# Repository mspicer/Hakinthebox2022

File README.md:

# Hack-in-the-box 2022 Badge Guide

- PCB.md contains the schematics and pcb layout for each board. This may be helpful for assembly or programming.
- PROGRAM.md contains information on flashing the boards with the current or custom code if desired.

## Assembly

### Step 1
- Solder the attiny85 to the base pcb.

### Step 2
- Solder the first two leds on the base pcb.

### Step 3
- Solder the last two leds on the base pcb.

### Step 4
- Solder the first two leds on the top of the upper pcb.

### Step 5
- Solder the next two leds on the top of the upper pcb.

### Step 6
- Solder the first two leds on the bottom of the upper pcb.

### Step 7
- Solder the last two leds on the upper pcb.

### Step 8
- Solder the headers on the board by first placing them in the expansion board or similar and then slide the board on to ensure good fit.

### Step 9

### Step 10
- Remove the stripped ends of the three solid-core wires and attach them to the base pcb.

### Step 11
- Solder the solid-core wires to the top. The easiest way is to solder the outer two wires, bend them all 90 degrees, then solder the middle one.

### Step 12
- Attach the stand offs to the base pcb with the socket cap screws.

### Step 13

### Step 14
- With the other screws attach the acrylic and the upper pcb to the standoffs.

### Step 15

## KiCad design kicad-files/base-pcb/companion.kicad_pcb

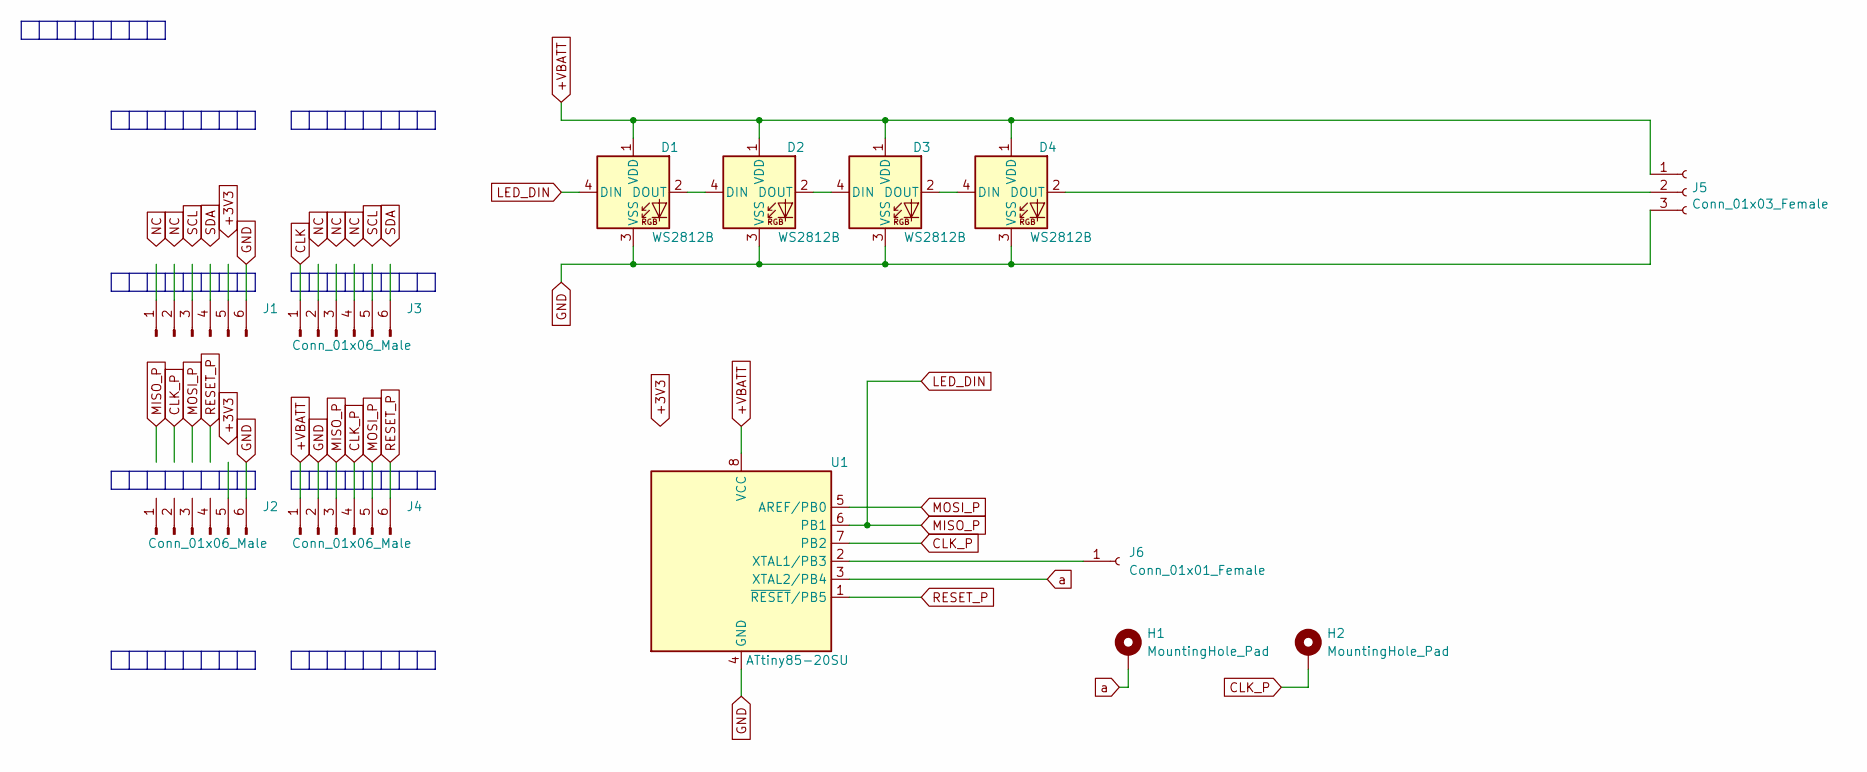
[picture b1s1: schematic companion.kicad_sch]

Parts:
D1, D2, D3, D4: WS2812B; LED_WS2812B_PLCC4_5.0x5.0mm_P3.2mm
H1, H2: MountingHole_Pad; MountingHole_4.3mm_M4_DIN965_Pad_TopOnly
J1, J2, J3, J4: Conn_01x06_Male; PinHeader_1x06_P2.54mm_Vertical
J5: Conn_01x03_Female; PinHeader_1x03_P2.54mm_Vertical_SMD_Pin1Left
J6: Conn_01x01_Female; SolderWirePad_1x01_SMD_1x2mm
U1: ATtiny85-20SU; SOIJ-8_5.3x5.3mm_P1.27mm

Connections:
+VBATT: D1.1 (VDD), D2.1 (VDD), D3.1 (VDD), D4.1 (VDD), J4.1, J5.1, U1.8 (VCC)
CLK: J3.1
CLK_P: H2.1, J4.4, U1.7 (PB2)
GND: D1.3 (VSS), D2.3 (VSS), D3.3 (VSS), D4.3 (VSS), J1.6, J2.6, J4.2, J5.3, U1.4 (GND)
LED_DIN: D1.4 (DIN), J4.3, U1.6 (PB1)
MOSI_P: J4.5, U1.5 (AREF/PB0)
unnamed: D1.2 (DOUT), D2.4 (DIN)
unnamed: D2.2 (DOUT), D3.4 (DIN)
unnamed: D3.2 (DOUT), D4.4 (DIN)
unnamed: D4.2 (DOUT), J5.2
unnamed: J6.1, U1.2 (XTAL1/PB3)
RESET_P: J4.6, U1.1 (~RESET/PB5)
a: H1.1, U1.3 (XTAL2/PB4)

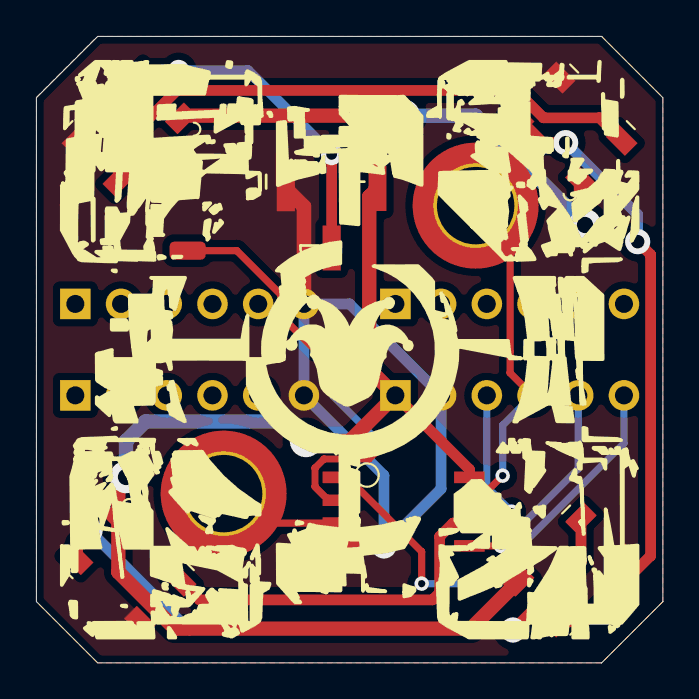
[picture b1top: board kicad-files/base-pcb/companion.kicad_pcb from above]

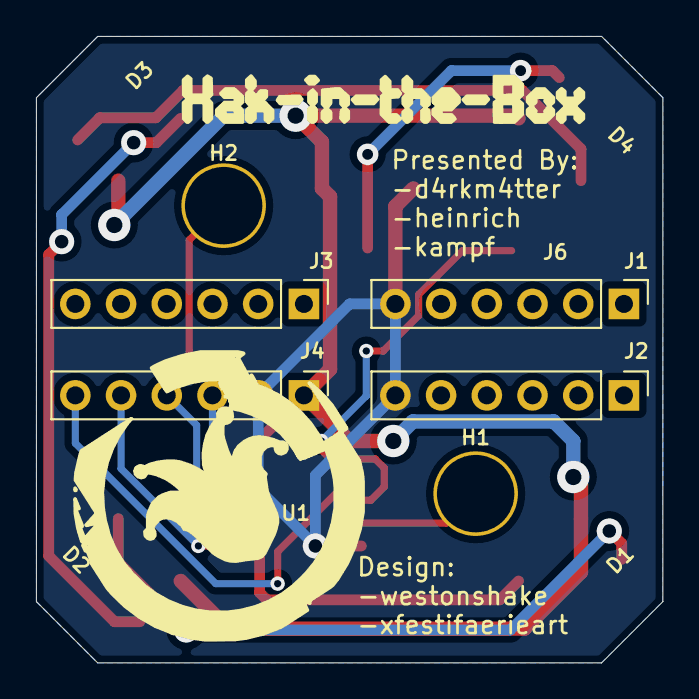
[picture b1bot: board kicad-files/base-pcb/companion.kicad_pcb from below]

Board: 2 copper layers, 34.8 x 34.8 mm, 13 parts (4 on the bottom side), 12 nets.

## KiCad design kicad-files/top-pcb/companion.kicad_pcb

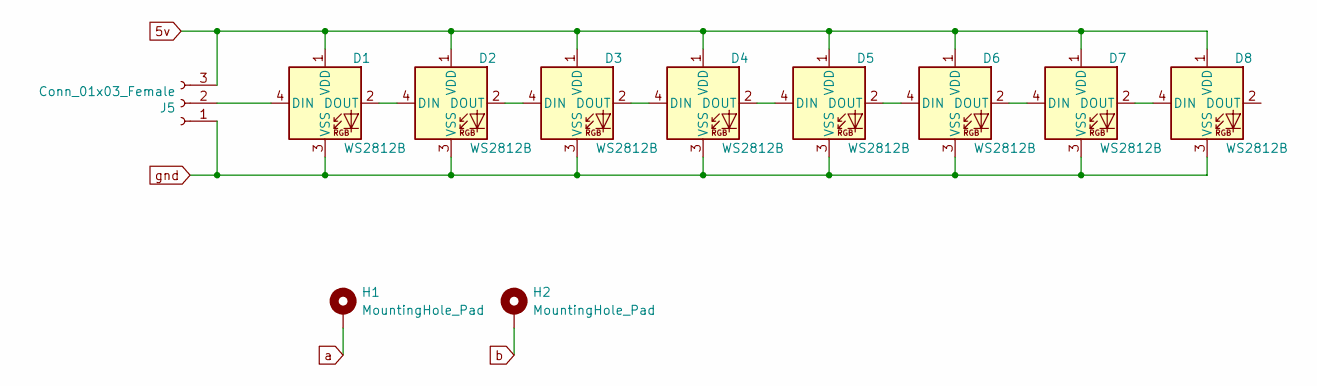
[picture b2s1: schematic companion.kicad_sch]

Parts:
D1, D2, D3, D4, D5, D6, D7, D8: WS2812B; LED_WS2812B_PLCC4_5.0x5.0mm_P3.2mm
H1, H2: MountingHole_Pad; MountingHole_4.3mm_M4_DIN965_Pad_TopOnly
J5: Conn_01x03_Female; PinHeader_1x03_P2.54mm_Vertical_SMD_Pin1Left

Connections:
5v: D1.1 (VDD), D2.1 (VDD), D3.1 (VDD), D4.1 (VDD), D5.1 (VDD), D6.1 (VDD), D7.1 (VDD), D8.1 (VDD), J5.3
unnamed: D1.2 (DOUT), D2.4 (DIN)
unnamed: D1.4 (DIN), J5.2
unnamed: D2.2 (DOUT), D3.4 (DIN)
unnamed: D3.2 (DOUT), D4.4 (DIN)
unnamed: D4.2 (DOUT), D5.4 (DIN)
unnamed: D5.2 (DOUT), D6.4 (DIN)
unnamed: D6.2 (DOUT), D7.4 (DIN)
unnamed: D7.2 (DOUT), D8.4 (DIN)
a: H1.1
b: H2.1
gnd: D1.3 (VSS), D2.3 (VSS), D3.3 (VSS), D4.3 (VSS), D5.3 (VSS), D6.3 (VSS), D7.3 (VSS), D8.3 (VSS), J5.1

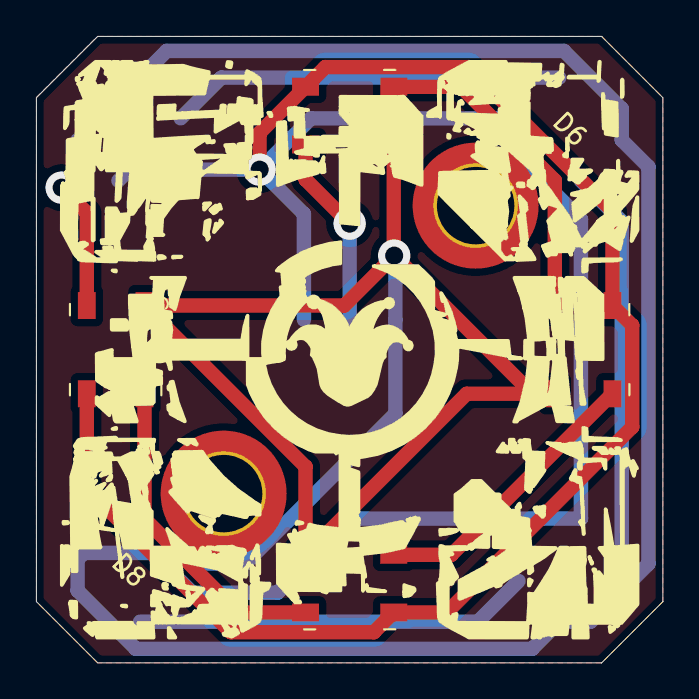
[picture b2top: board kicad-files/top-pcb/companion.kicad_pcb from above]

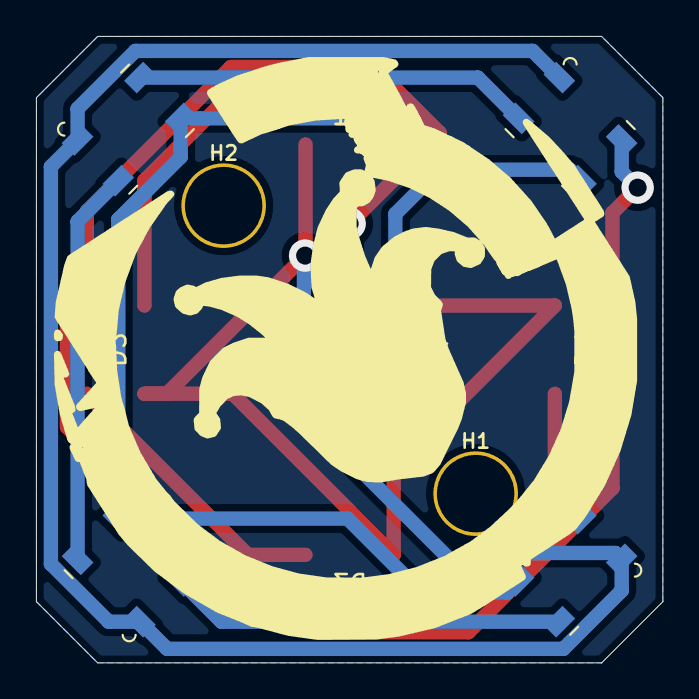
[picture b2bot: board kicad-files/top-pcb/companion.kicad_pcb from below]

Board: 2 copper layers, 34.8 x 34.8 mm, 11 parts (5 on the bottom side), 10 nets.

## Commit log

2022-10-24 kicad files
2022-10-25 added assembly images
2022-10-25 added code
2022-10-25 added header image
2022-10-25 added programming settings
